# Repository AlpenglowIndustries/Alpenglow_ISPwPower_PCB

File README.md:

# Alpenglow_ISPwPower
A breadboard-compatible ISP header which keys into the power rail and has a switch to connect/disconnect Vcc.

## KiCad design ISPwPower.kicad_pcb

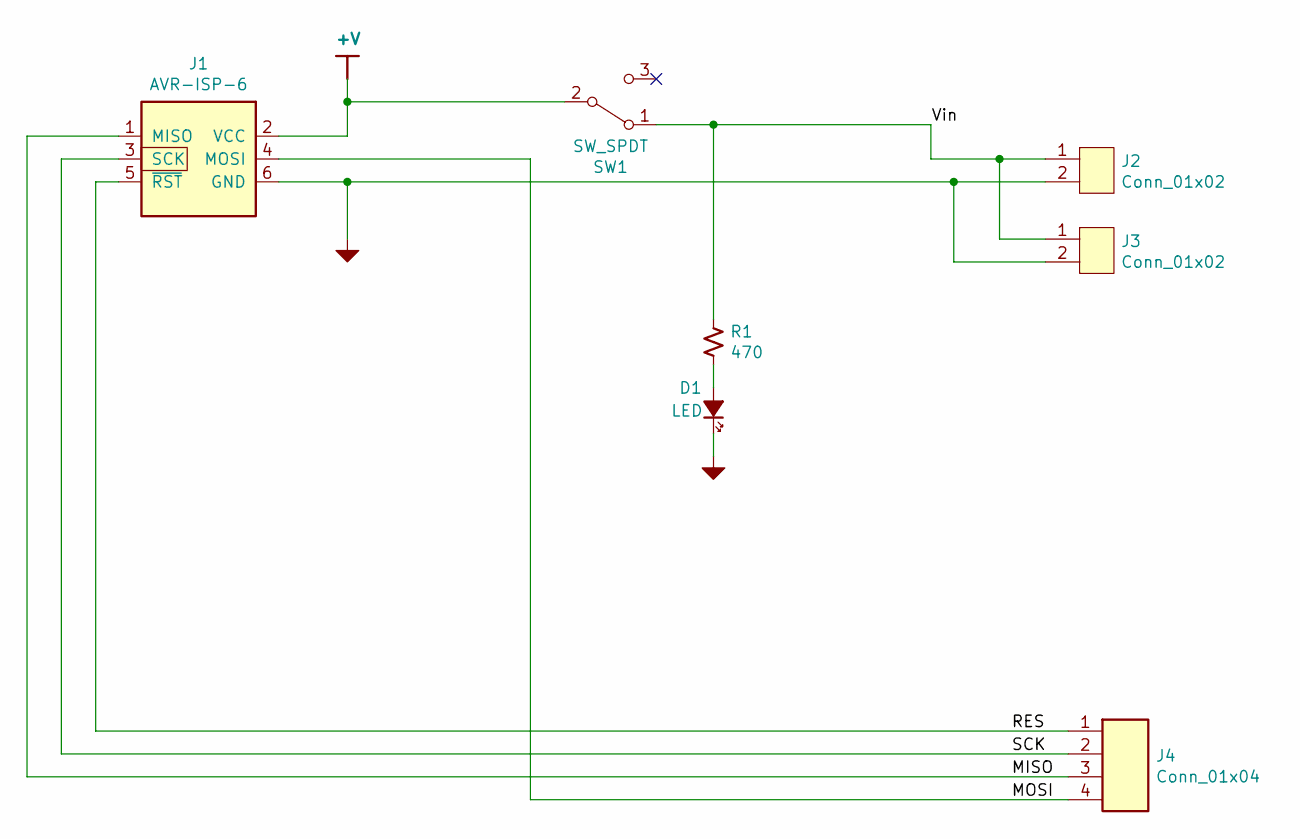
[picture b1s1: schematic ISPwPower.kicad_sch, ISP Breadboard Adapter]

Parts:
D1: LED; LED_D3.0mm
J1: AVR-ISP-6; IDC-Header_2x03_P2.54mm_Vertical
J2, J3: Conn_01x02; Conn_1x02
J4: Conn_01x04; Conn_1x04_THRU
R1: 470; R_Axial_DIN0204_L3.6mm_D1.6mm_P2.54mm_Vertical
SW1: SW_SPDT; SW_SLIDE_RTA

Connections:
+V: J1.2 (VCC), SW1.2 (B)
/MISO: J1.1 (MISO), J4.3
/MOSI: J1.4 (MOSI), J4.4
/RES: J1.5 (~RST), J4.1
/SCK: J1.3 (SCK), J4.2
/Vin: J2.1, J3.1, R1.1, SW1.1 (A)
GND: D1.1 (K), J1.6 (GND), J2.2, J3.2
unnamed: D1.2 (A), R1.2

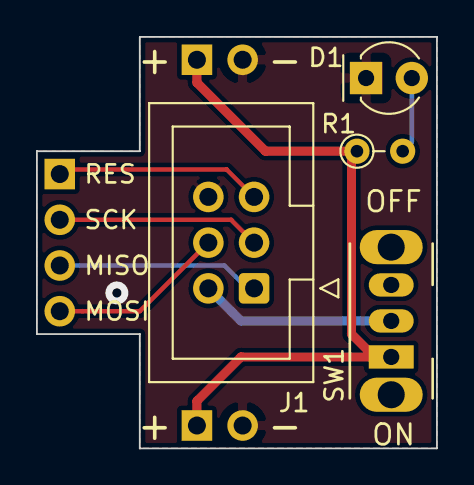
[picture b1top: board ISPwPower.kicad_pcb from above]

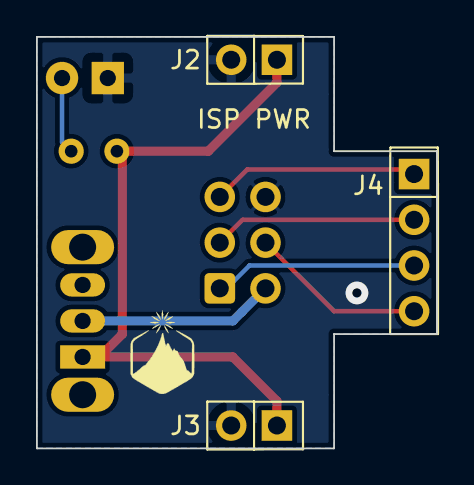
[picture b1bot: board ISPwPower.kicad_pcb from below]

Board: 2 copper layers, 22.2 x 22.9 mm, 7 parts (3 on the bottom side), 8 nets.

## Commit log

2021-11-01 ignoring zip files
2022-10-26 Updated to add final gerbers
2022-10-26 BOM and Schematic
2022-10-27 Updated gitignore, changed BOM to CSV file
